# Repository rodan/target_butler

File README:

Target butler is an archery-related project that tries to 'read' the arrow score based on sound and vibration sensor readouts.
  4 sensors (microphones) are surrounding the target itself, each of the 4 channels are amplified and the resulting signal passes thru an envelope-detection circuit. the 4 ADC values are read at a ~1ms interval by the uC.
  power is either from a 2Ah LiPo accu, any random 5V source or a solar panel.

  this project has not reached a 'working' stage. the sensors need to be changed to something that has a more omni-directional quality.

  Library dependencies for the included avr software:

  rfm12b      http://jeelabs.org/2009/02/10/rfm12b-library-for-arduino/
  sdfatlib    http://code.google.com/p/sdfatlib/

  dependencies for the server-side software:

  // not written yet

  Author:          Petre Rodan <2b4eda@subdimension.ro>
  Available from:  https://github.com/rodan/target_butler
  License:         GNU GPLv3

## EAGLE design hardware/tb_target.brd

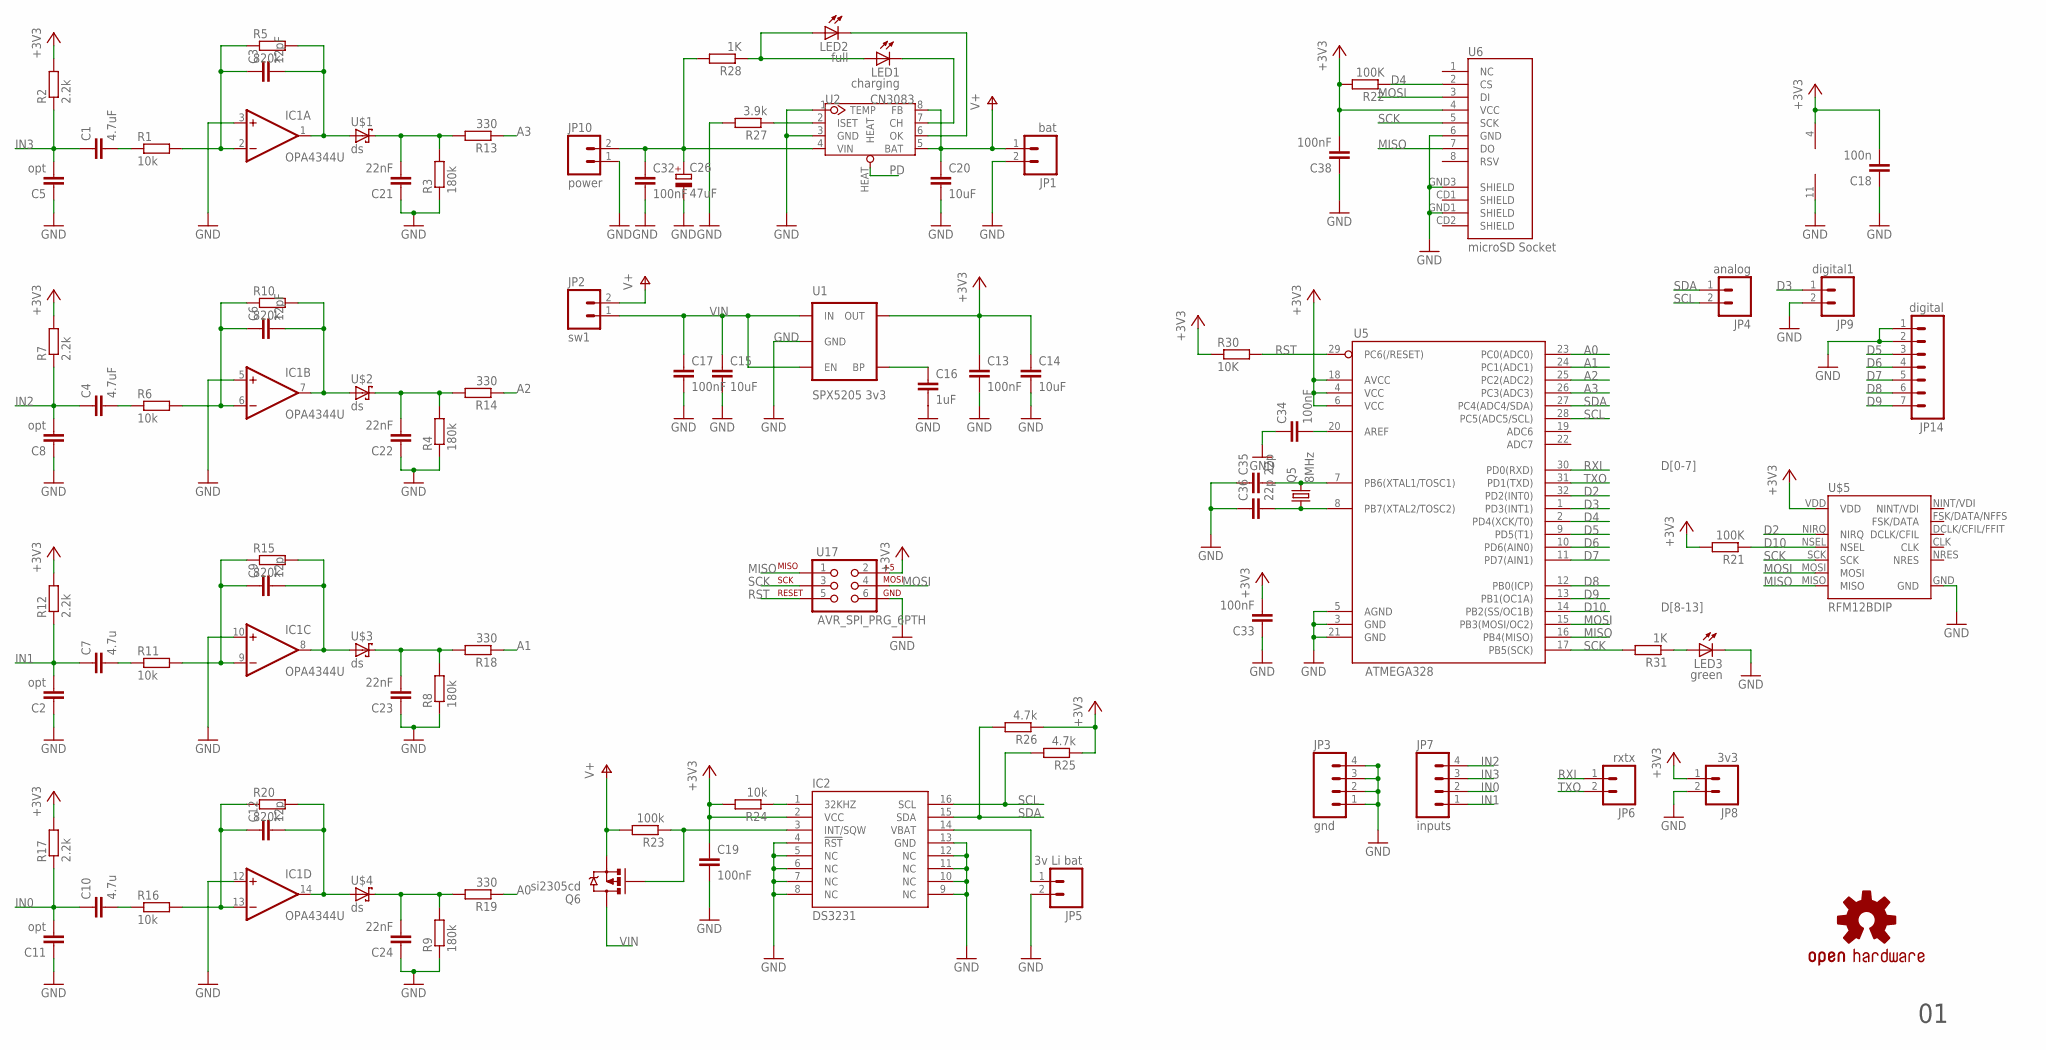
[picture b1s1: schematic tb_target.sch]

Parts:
C1, C4: 4.7uF; C0805
C2, C5, C8, C11: opt; C0805
C3, C6: 12pF; C0805
C7, C10: 4.7u; C0805
C9, C12: 12p; C0805
C13, C17, C19, C32, C33, C34, C38: 100nF; C0805
C14, C15, C20: 10uF; C1206
C16: 1uF; C0805
C18: 100n; C0805
C21, C22, C23, C24: 22nF; C0805
C26: 47uF; CT7343
C35, C36: 22p; C0805
IC1: OPA4344U; SO14
IC2: DS3231; SO-16
JP1: bat; 1X02
JP2: sw1; 1X02
JP3: gnd; 1X04
JP4: analog; 1X02
JP5: 3v Li bat; 1X02
JP6: rxtx; 1X02
JP7: inputs; 1X04
JP8: 3v3; 1X02
JP9: digital1; 1X02
JP10: power; 1X02
JP14: digital; 1X07
LED1: charging; CHIP-LED0805
LED2: full; CHIP-LED0805
LED3: green; CHIP-LED0805
Q5: 8MHz; CRYSTAL_5X3.2
Q6: si2305cd; SOT23-3_POWER
R1, R6, R11, R16, R24: 10k; R0805W
R2, R7, R12, R17: 2.2k; R0805W
R3, R4, R8, R9: 180k; R0805W
R5, R10, R15, R20: 820k; R0805W
R13, R14, R18, R19: 330; R0805W
R21, R22: 100K; R0805W
R23: 100k; R0805W
R25, R26: 4.7k; R0805W
R27: 3.9k; R0805W
R28, R31: 1K; R0805W
R30: 10K; R0805W
U1: SPX5205 3v3; SOT23-5
U2: CN3083; SOP8-W/-HEAT
U5: ATMEGA328; TQFP32-08
U6: microSD Socket; MICRO-SD-SOCKET-PP
U17: AVR_SPI_PRG_6PTH; 2X3
U$1, U$2, U$3, U$4: ds; SOD80
U$5: RFM12BDIP; RFM12B_DIP
U$7: OSHW-LOGOM; OSHW-LOGO-M

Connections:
+3V3: C13.1, C14.1, C18.2, C19.1, C33.2, C38.2, IC1.4 (V+), IC2.2 (VCC), JP8.1, R2.2, R7.2, R12.2, R17.2, R21.2, R22.2, R24.2, R25.1, R26.1, R30.1, U1.5 (OUT), U5.4 (VCC), U5.6 (VCC), U5.18 (AVCC), U6.4 (VCC), U17.2, U$5.VDD
A0: R19.1, U5.23 (PC0(ADC0))
A0D: C24.2, R9.2, R19.2, U$4.C
A1: R18.1, U5.24 (PC1(ADC1))
A1D: C23.2, R8.2, R18.2, U$3.C
A2: R14.1, U5.25 (PC2(ADC2))
A2D: C22.2, R4.2, R14.2, U$2.C
A2E: C6.2, IC1.7 (OUT), R10.2, U$2.A
A3: R13.1, U5.26 (PC3(ADC3))
A3D: C21.2, R3.2, R13.2, U$1.C
D2: U5.32 (PD2(INT0)), U$5.NIRQ
D3: JP9.1, U5.1 (PD3(INT1))
D4: R22.1, U5.2 (PD4(XCK/T0)), U6.2 (CS)
D5: JP14.3, U5.9 (PD5(T1))
D6: JP14.4, U5.10 (PD6(AIN0))
D7: JP14.5, U5.11 (PD7(AIN1))
D8: JP14.6, U5.12 (PB0(ICP))
D9: JP14.7, U5.13 (PB1(OC1A))
D10: R21.1, U5.14 (PB2(SS/OC1B)), U$5.NSEL
GND: C2.1, C5.1, C8.1, C11.1, C13.2, C14.2, C15.2, C16.2, C17.2, C18.1, C19.2, C20.2, C21.1, C22.1, C23.1, C24.1, C26.-, C32.2, C33.1, C34.1, C35.1, C36.1, C38.1, IC1.3 (+IN), IC1.5 (+IN), IC1.10 (+IN), IC1.11 (V-), IC1.12 (+IN), IC2.4 (!RST), IC2.5 (NC), IC2.6 (NC), IC2.7 (NC), IC2.8 (NC), IC2.9 (NC), IC2.10 (NC), IC2.11 (NC), IC2.12 (NC), IC2.13 (GND), JP1.2, JP3.1, JP3.2, JP3.3, JP3.4, JP5.2, JP8.2, JP9.2, JP10.1, JP14.1, JP14.2, LED3.C, R3.1, R4.1, R8.1, R9.1, R27.2, U1.2 (GND), U2.1 (TEMP), U2.3 (GND), U5.3 (GND), U5.5 (AGND), U5.21 (GND), U6.6 (GND), U6.GND1 (SHIELD), U6.GND3 (SHIELD), U17.6, U$5.GND
IN0: C10.1, C11.2, JP7.2, R17.1
IN1: C2.2, C7.1, JP7.1, R12.1
IN2: C4.1, C8.2, JP7.4, R7.1
IN3: C1.1, C5.2, JP7.3, R2.1
MISO: U5.16 (PB4(MISO)), U6.7 (DO), U17.1, U$5.MISO
MOSI: U5.15 (PB3(MOSI/OC2)), U6.3 (DI), U17.4, U$5.MOSI
unnamed: C16.1, U1.4 (BP)
unnamed: C1.2, R1.1
unnamed: C3.1, IC1.2 (-IN), R1.2, R5.1
unnamed: IC2.1 (32KHZ), R24.1
unnamed: IC2.3 (INT/SQW), Q6.1 (G), R23.1
unnamed: C4.2, R6.1
unnamed: C6.1, IC1.6 (-IN), R6.2, R10.1
unnamed: IC2.14 (VBAT), JP5.1
unnamed: R27.1, U2.2 (ISET)
unnamed: C7.2, R11.1
unnamed: C9.1, IC1.9 (-IN), R11.2, R15.1
unnamed: C26.+, C32.1, JP10.2, R28.2, U2.4 (VIN)
unnamed: LED1.A, LED2.A, R28.1
unnamed: C10.2, R16.1
unnamed: C12.1, IC1.13 (-IN), R16.2, R20.1
unnamed: LED1.C, U2.7 (CH)
unnamed: LED2.C, U2.6 (OK)
unnamed: C36.2, Q5.P$1 (1), U5.8 (PB7(XTAL2/TOSC2))
unnamed: C35.2, Q5.P$2 (2), U5.7 (PB6(XTAL1/TOSC1))
unnamed: C34.2, U5.20 (AREF)
unnamed: LED3.A, R31.1
unnamed: C3.2, IC1.1 (OUT), R5.2, U$1.A
unnamed: C9.2, IC1.8 (OUT), R15.2, U$3.A
unnamed: C12.2, IC1.14 (OUT), R20.2, U$4.A
PD: U2.HEAT
RST: R30.2, U5.29 (PC6(/RESET)), U17.5
RXI: JP6.1, U5.30 (PD0(RXD))
SCK: R31.2, U5.17 (PB5(SCK)), U6.5 (SCK), U17.3, U$5.SCK
SCL: IC2.16 (SCL), JP4.2, R25.2, U5.28 (PC5(ADC5/SCL))
SDA: IC2.15 (SDA), JP4.1, R26.2, U5.27 (PC4(ADC4/SDA))
TXO: JP6.2, U5.31 (PD1(TXD))
V+: C20.1, JP1.1, JP2.2, Q6.2 (S), R23.2, U2.5 (BAT), U2.8 (FB)
VIN: C15.1, C17.1, JP2.1, Q6.3 (D), U1.1 (IN), U1.3 (EN)

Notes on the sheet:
D[0-7]
D[8-13]

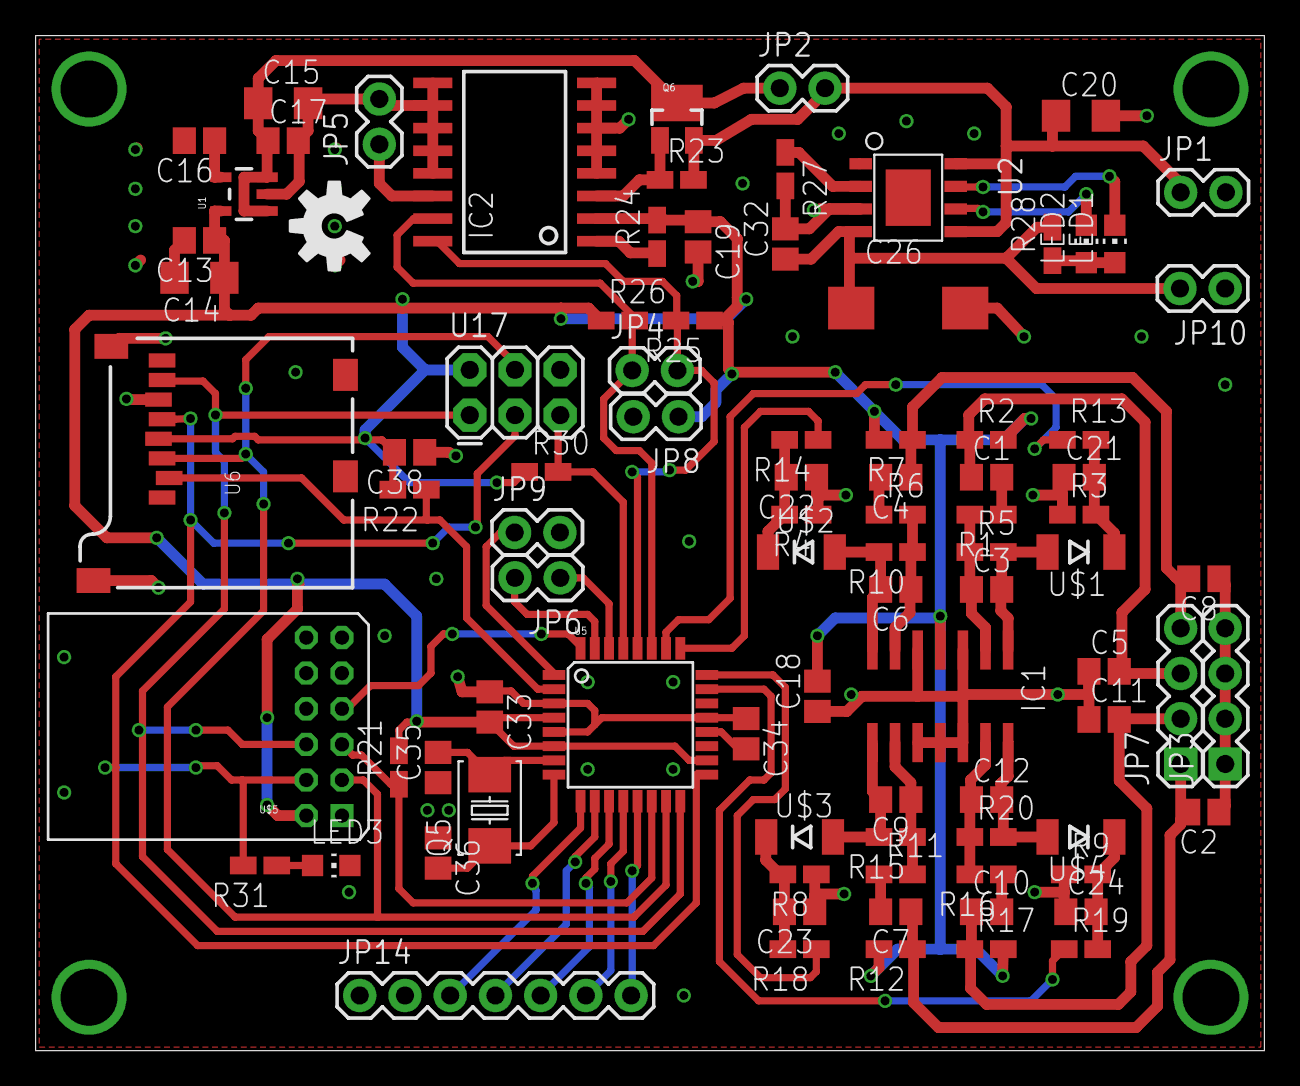
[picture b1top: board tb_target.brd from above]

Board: 2 copper layers, 69.0 x 57.0 mm, 90 parts (0 on the bottom side), 58 nets.

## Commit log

2012-09-13 avr part added
2012-10-29 disappointing first trials
2013-10-24 omg, someone starred this
2018-09-01 email change

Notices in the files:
parts and their libraries:
SparkFun-Connectors: Licensing: CC v3.0 Share-Alike You are welcome to use this library for commercial purposes.
